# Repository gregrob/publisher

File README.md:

# Publisher

IoT gadget that sends / receives / acts on MQTT messages.

Using arduino library and PlatformIO to allow easy porting between ESP8266 / ESP32 / Raspberry Pi Pico.

Applications:

1. Alarm interface
* PIR states.
* Remote arm / disarm.

2. Garage door
* Door state.
* Open / Close.

3. Tank Water Level
* Water level.

## Documentation

Detailed technical documentation for various system components and features:

### Device Control & Management
- **[Reset Control via MQTT](docs/reset_control/reset_control_mqtt.md)** - Remote device reset functionality including WiFi and NVM clearing

### Hawkbit
- **[Hawkbit Client Flow](docs/hawkbit/hawkbit_client_flow.svg)** - Over-the-air (OTA) update client flow diagram showing device update process with hawkbit

### Communication Protocols
- *(coming soon)*

### Hardware Interfaces  
- *(coming soon)*

### System Features
- *(coming soon)*

### Development & Debugging
- *(coming soon)*

### Integration Examples
- *(coming soon)*

## Software Architecture

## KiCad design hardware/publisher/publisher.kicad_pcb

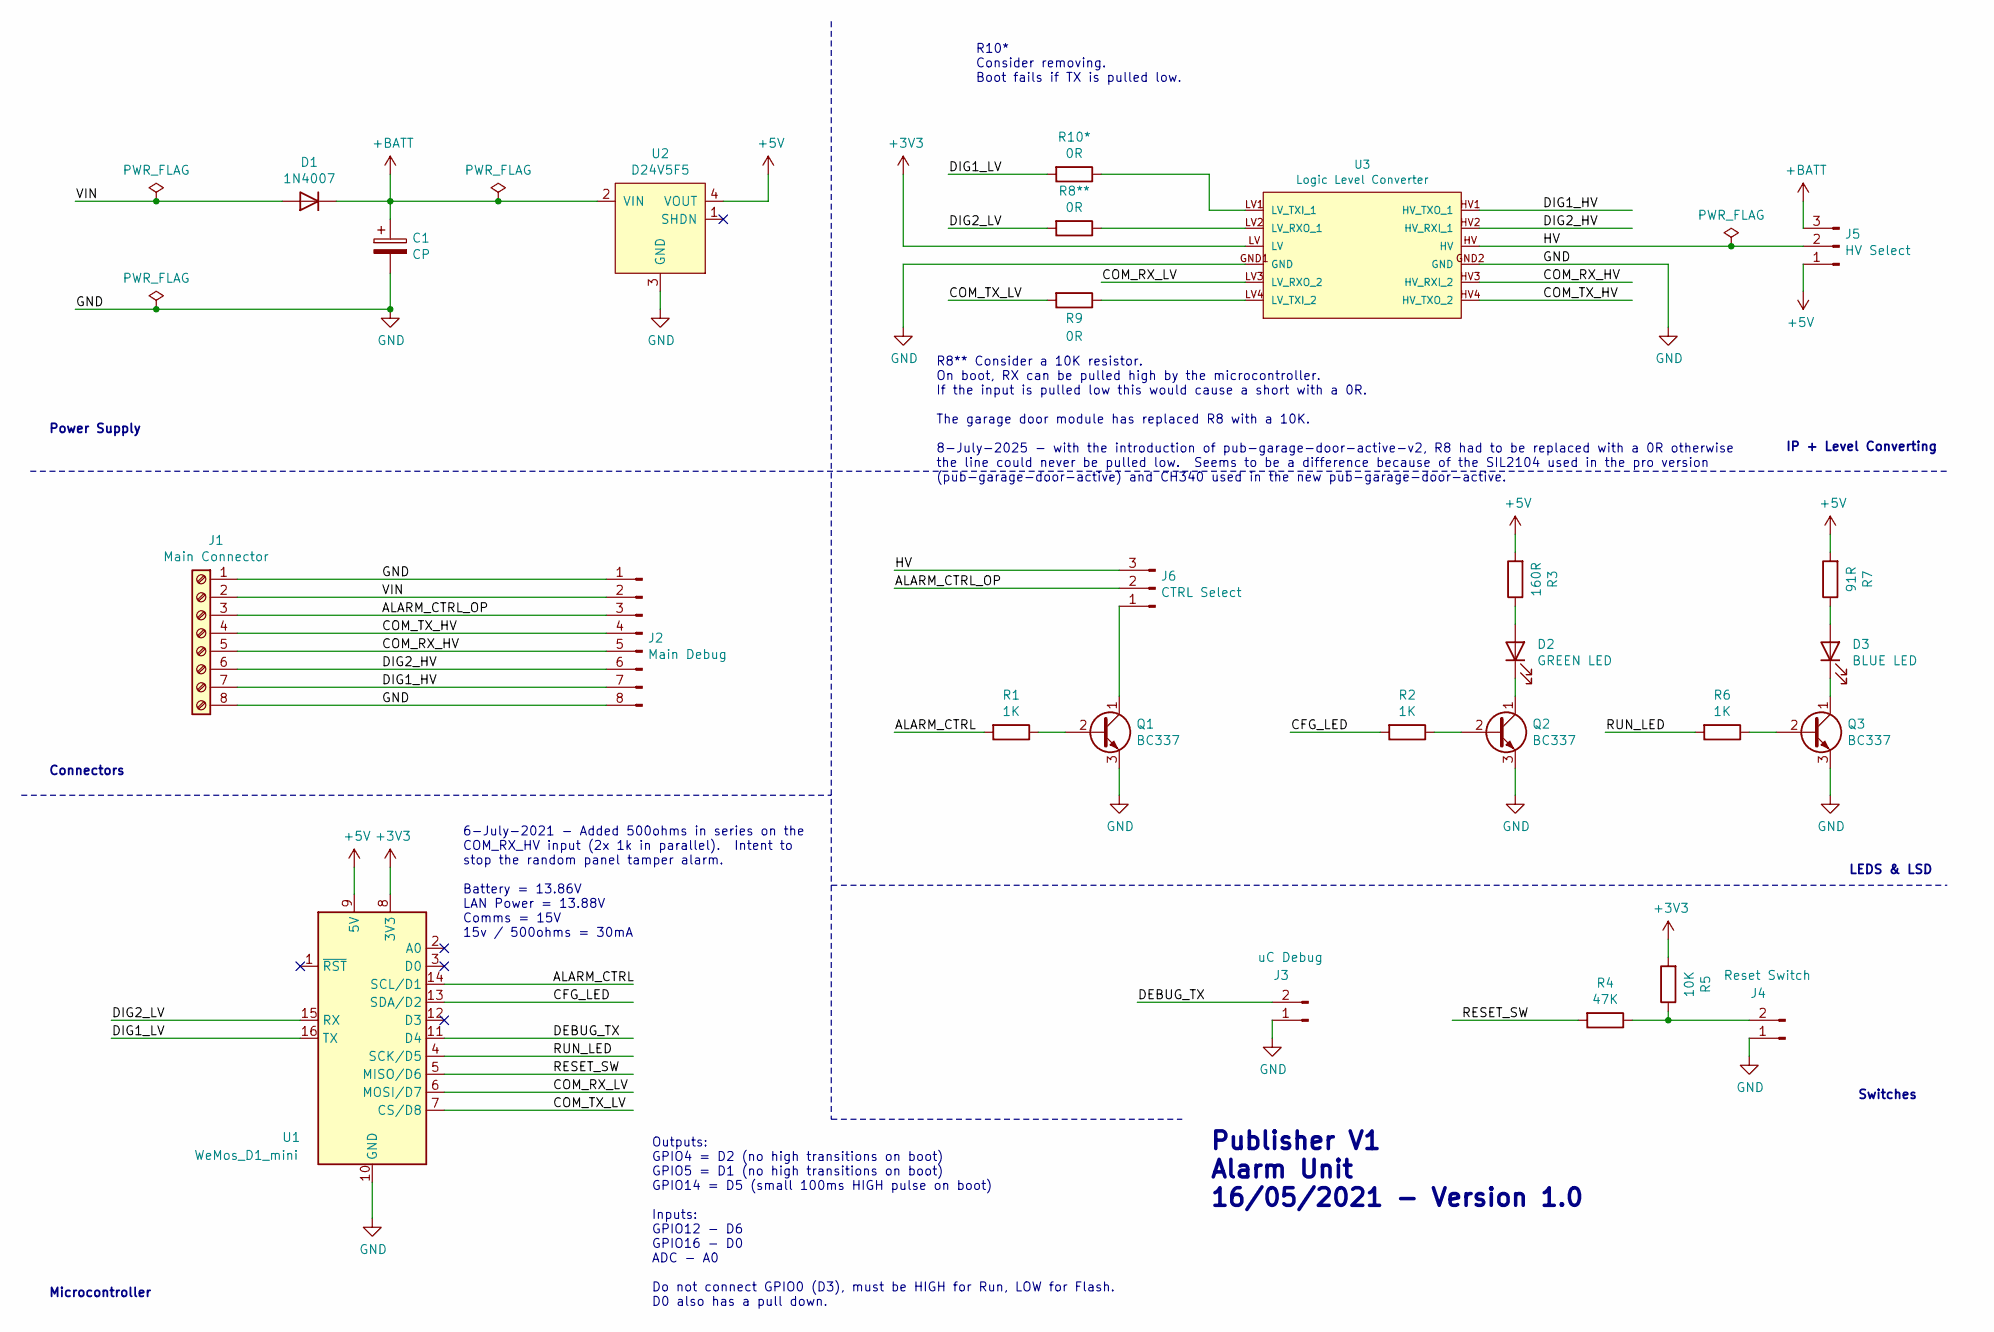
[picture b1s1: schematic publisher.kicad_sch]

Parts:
C1: CP; CP_Radial_D8.0mm_P3.50mm
D1: 1N4007; D_DO-41_SOD81_P10.16mm_Horizontal
D2: GREEN LED; LED_D3.0mm_Clear
D3: BLUE LED; LED_D3.0mm_Clear
J1: Main Connector; TerminalBlock_Phoenix_MPT-0,5-8-2.54_1x08_P2.54mm_Horizontal
J2: Main Debug; PinHeader_1x08_P2.54mm_Vertical
J3: uC Debug; PinHeader_1x02_P2.54mm_Vertical
J4: Reset Switch; PinHeader_1x02_P2.54mm_Vertical
J5: HV Select; PinHeader_1x03_P2.54mm_Vertical
J6: CTRL Select; PinHeader_1x03_P2.54mm_Vertical
Q1, Q2, Q3: BC337; TO-92_Inline_Wide
R1, R2, R6: 1K; R_Axial_DIN0207_L6.3mm_D2.5mm_P10.16mm_Horizontal
R3: 160R; R_Axial_DIN0207_L6.3mm_D2.5mm_P10.16mm_Horizontal
R4: 47K; R_Axial_DIN0207_L6.3mm_D2.5mm_P10.16mm_Horizontal
R5: 10K; R_Axial_DIN0207_L6.3mm_D2.5mm_P10.16mm_Horizontal
R7: 91R; R_Axial_DIN0207_L6.3mm_D2.5mm_P10.16mm_Horizontal
R8**, R9, R10*: 0R; R_Axial_DIN0207_L6.3mm_D2.5mm_P10.16mm_Horizontal
U1: WeMos_D1_mini; WEMOS_D1_mini_light
U2: D24V5F5
U3: Logic Level Converter; SPARKFUN_LOGIC_LEVEL_CONVERTER

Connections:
+3V3: R5.2, U1.8 (3V3), U3.LV
+5V: J5.1, R3.2, R7.2, U1.9 (5V), U2.4 (VOUT)
+BATT: C1.1, D1.1 (K), J5.3, U2.2 (VIN)
/ALARM_CTRL: R1.2, U1.14 (SCL/D1)
/ALARM_CTRL_OP: J1.3, J2.3, J6.2
/CFG_LED: R2.2, U1.13 (SDA/D2)
/COM_RX_HV: J1.5, J2.5, U3.HV3 (HV_RXI_2)
/COM_RX_LV: U1.6 (MOSI/D7), U3.LV3 (LV_RXO_2)
/COM_TX_HV: J1.4, J2.4, U3.HV4 (HV_TXO_2)
/COM_TX_LV: R9.2, U1.7 (CS/D8)
/DEBUG_TX: J3.2, U1.11 (D4)
/DIG1_HV: J1.7, J2.7, U3.HV1 (HV_TXO_1)
/DIG1_LV: R10*.2, U1.16 (TX); also elsewhere on the board
/DIG2_HV: J1.6, J2.6, U3.HV2 (HV_RXI_1)
/DIG2_LV: R8**.2, U1.15 (RX); also elsewhere on the board
/HV: J5.2, J6.3, U3.HV
/RESET_SW: R4.2, U1.5 (MISO/D6)
/RUN_LED: R6.2, U1.4 (SCK/D5)
/VIN: D1.2 (A), J1.2, J2.2
GND: C1.2, J1.1, J1.8, J2.1, J2.8, J3.1, J4.1, Q1.3 (E), Q2.3 (E), Q3.3 (E), U1.10 (GND), U2.3 (GND), U3.GND1 (GND), U3.GND2 (GND)
unnamed: D2.1 (K), Q2.1 (C)
unnamed: D2.2 (A), R3.1
unnamed: D3.1 (K), Q3.1 (C)
unnamed: D3.2 (A), R7.1
unnamed: J4.2, R4.1, R5.1
unnamed: J6.1, Q1.1 (C)
unnamed: Q1.2 (B), R1.1
unnamed: Q2.2 (B), R2.1
unnamed: Q3.2 (B), R6.1
unnamed 29: R8**.1, U3.LV2 (LV_RXO_1); also elsewhere on the board
unnamed: R9.1, U3.LV4 (LV_TXI_2)
unnamed 31: R10*.1, U3.LV1 (LV_TXI_1); also elsewhere on the board

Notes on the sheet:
Power Supply
IP + Level Converting
R8** Consider a 10K resistor. On boot, RX can be pulled high by the microcontroller. If the input is pulled low this would cause a short with a 0R. The garage door module has replaced R8 with a 10K. 8-July-2025 - with the introduction of pub-garage-door-active-v2, R8 had to be replaced with a 0R ot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
Outputs: GPIO4 = D2 (no high transitions on boot) GPIO5 = D1 (no high transitions on boot) GPIO14 = D5 (small 100ms HIGH pulse on boot) Inputs: GPIO12 - D6 GPIO16 - D0 ADC - A0 Do not connect GPIO0 (D3), must be HIGH for Run, LOW for Flash. D0 also has a pull down.
6-July-2021 - Added 500ohms in series on the COM_RX_HV input (2x 1k in parallel). Intent to stop the random panel tamper alarm. Battery = 13.86V LAN Power = 13.88V Comms = 15V 15v / 500ohms = 30mA
Connectors
Switches
LEDS & LSD
Publisher V1 Alarm Unit 16/05/2021 - Version 1.0
R10* Consider removing. Boot fails if TX is pulled low.
Microcontroller

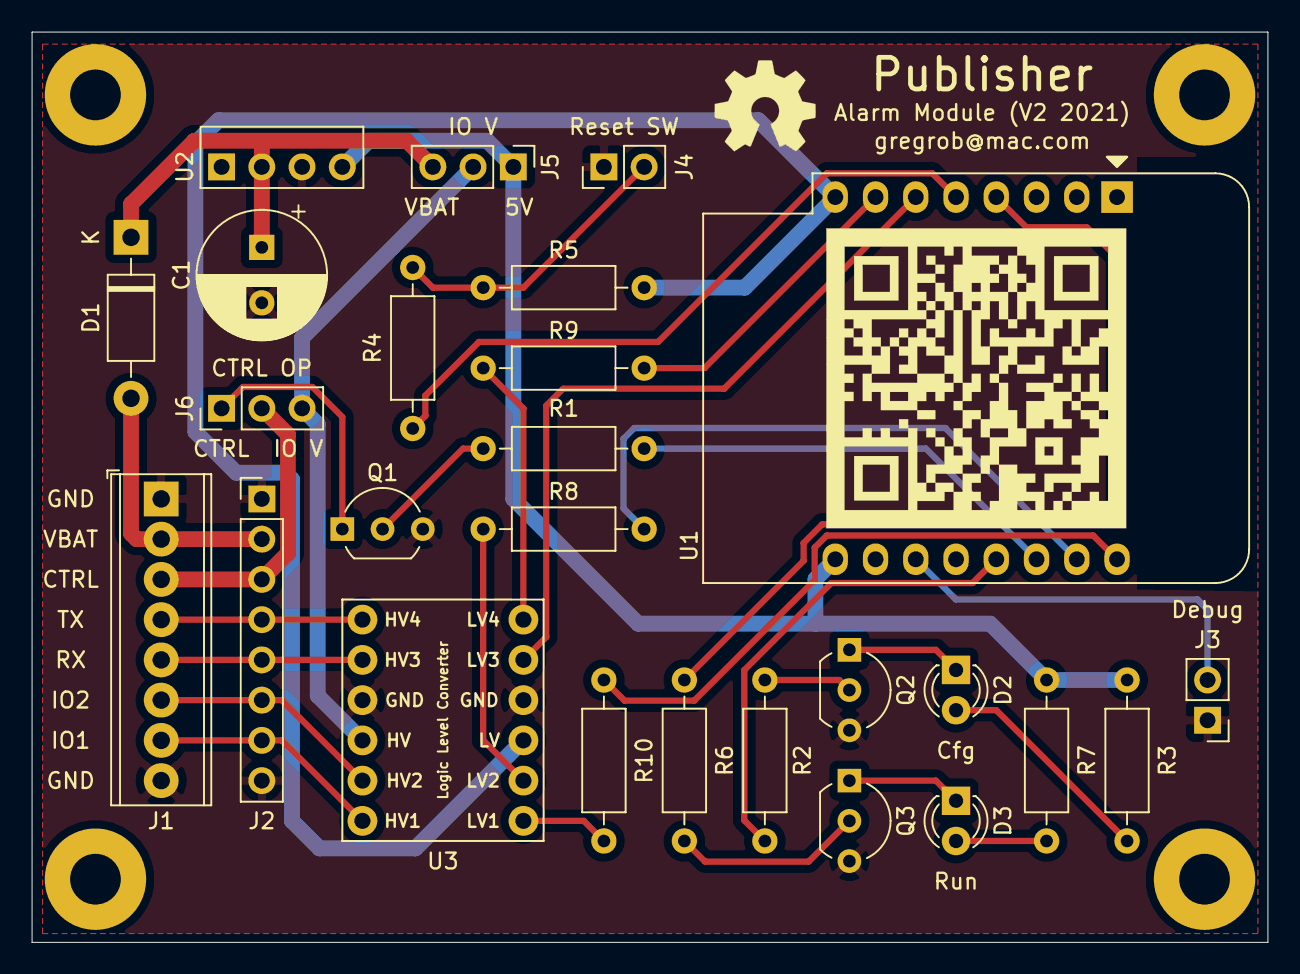
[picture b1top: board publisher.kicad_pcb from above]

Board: 2 copper layers, 78.0 x 57.5 mm, 30 parts (0 on the bottom side), 32 nets.

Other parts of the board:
H1, H2, H3, H4: MountingHole_3.2mm_M3_Pad
R8, R10: 0R; R_Axial_DIN0207_L6.3mm_D2.5mm_P10.16mm_Horizontal

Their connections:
/DIG1_LV: R10.2; also elsewhere on the board
/DIG2_LV: R8.2; also elsewhere on the board
unnamed 29: R8.1; also elsewhere on the board
unnamed 31: R10.1; also elsewhere on the board

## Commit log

2021-03-14 Initial setup of mqtt and wifi.
2021-03-15 Improved debug code.
2021-03-16 Updated with new debug module.
2021-03-16 Clean up and updated with new json attributes.
2021-03-18 First cut of OTA software, still WIP.
2021-03-19 OTA cleanup including credentials template.
2021-03-19 Cleanup of build scripts and main.
2021-03-21 Alarm interface added.
2021-03-26 Improvements to the alarm including arm/disarm.
2021-03-26 Runtime stuff and incremental improvements.
2021-03-26 Alarm message integration.
2021-03-27 Runtime in a module and publish on MQTT.
2021-03-27 Small clean up.
2021-03-27 One shot alarm arm / disarm.
2021-03-27 Fixed bug to stop one shot update when its active.
2021-03-27 Clean out debug code.
2021-04-04 Addition of new modules.
2021-04-05 Experiment with wifi manager.
2021-04-06 MQTT clean-up and additional functions.
2021-04-06 Incremental updates.
2021-04-06 WiFi improvements and update to wifi manager.
2021-04-07 Better handling of TX messages.
2021-04-07 Defines for JSON variable names.
2021-04-07 Integration of wifi message.
2021-04-07 Cleanup.
2021-04-07 Cleanup and removal of old functioanlity.
2021-04-07 Updated alarm OTA.
2021-04-07 Small cleanup.
2021-04-07 Alarm TX message handler updated.
2021-04-07 Support for SSID in module wifi messaging.
2021-04-09 Integraiton of outputs controller.
2021-04-09 Fixed python script so it works on Win and Linux.
2021-04-10 Added input handler.
2021-04-10 Small outputs tidy up.
2021-04-13 Initial NVM driver.
2021-04-14 NVM handler made modular.
2021-04-15 Additional NVM features.
2021-04-15 Added architecture.
2021-04-15 NVM map updated.
2021-04-15 Initial readme.
2021-04-15 NVM include cleanup.
2021-04-16 NVM map tweak.
2021-04-16 Utils.
2021-04-16 NVM handler tracking errors.
2021-04-16 WiFi and MQTT updated for NVM config.
2021-04-16 OTA updated to use NVM.
2021-04-16 Added NVM status MQTT message.
2021-04-16 Tidy.
2021-04-17 NVM version and messaging improvements.
2021-04-17 Diagram updates.
2021-04-17 Fixed variable names.
2021-04-17 Output driver improvements.
2021-04-17 Configs for LED brightness and control.
2021-04-17 Remapped outputs (port limitations during boot).
2021-04-17 Diagram updated with outputs.
2021-04-17 Small tidyup.
2021-04-17 Fixed some wrong comments.
2021-04-17 Improved input handler.
2021-04-17 Architecture update.
2021-04-19 NVM method for clearing and config updates.
2021-04-19 More methods.
2021-04-19 Integration of reset handler.
2021-04-19 Unique names in the state enum.
2021-04-19 Removed blinking run LED.
2021-04-19 Wifi connected status.
2021-04-19 Status controller added.
2021-04-19 Diagram updated.
2021-04-24 Initial cut of hawkbit.
2021-04-24 Hawkbit http handler improvements.
2021-04-25 Hawkbit client interum update.
2021-04-25 More hawkbit improvements.
2021-04-26 Debug handler improvement.
2021-04-26 Debug handler incremental improvement.
2021-04-26 Improved hawkbit and version.
2021-04-26 Hawkbit poll interval adjusted.
2021-05-28 Small tweaks.
2021-05-28 More small tweaks.
2021-05-31 LWT added to MQTT.
2021-06-03 Reset controller integration with hawkbit.
2021-06-03 Alarm configuraiton moved to NVM.
2021-06-04 Alarm sounding status.
2021-06-05 Alarm functionality for triggers and sounding.
2021-06-05 Optomised alarm PIR and source trigger handling.
2021-06-05 Alarm message optomisation.
2021-06-05 Bug fix for module identified too late in init.
2021-06-06 Hawkbit configuration moved to NVM.
2021-07-06 Hardware (in kicad) added.
2021-07-06 D1 mini library added.
2021-07-06 Added sparkfun library.
2022-08-20 added garage door module and ultrasonics test code
2022-08-20 added 000.007.005 binary
2022-08-21 added 000.006.005 bin and readme for all releases
2022-08-23 schematic notes for 10k on R8 and removing R10
2022-09-08 fix incorrectly configured input debounce reset
2022-09-08 include release notes for 000.007.006
2025-07-07 pin the framework version to espressif8266@2.6.3 as new versions need a bit rework of include files
2025-07-07 added hawkbit docco
2025-07-07 hardware backup
2025-07-07 kicad updated project files
2025-07-07 settings for pub-garage-door-v2
2025-07-08 added documentation section
2025-07-08 upgraded sch and pcb to kicad 8
